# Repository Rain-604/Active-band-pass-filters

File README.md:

# Active Band-Pass Filter Design

## Project Overview
This project showcases a complete hardware design cycle for an Active Band-Pass Filter using the **TL072 Operational Amplifier**. It transition from theoretical calculations to a fully routed PCB layout ready for manufacturing.

## Key Design Features
*   **Active Stage:** Utilizes a TL072 dual op-amp for high input impedance and low noise.
*   **Variable Tuning:** Includes a 10kΩ potentiometer (RV1) for adjustable gain/frequency response tuning.
*   **Signal Integrity:** Optimized 2-layer PCB layout with a dedicated ground plane to minimize noise interference.

## Design Files
### 1. Schematic Design
The schematic features a dual-supply op-amp configuration (powered via the 9V Power block) with a High-Pass stage (C1/R3/R4) and a Low-Pass stage (C2/R5/RV1).

### 2. PCB Layout
The board is designed for manual assembly using through-hole components. 
*   **Trace Width:** Sized for reliable signal delivery and ease of soldering.
*   **Component Placement:** Logically grouped to keep signal paths short.

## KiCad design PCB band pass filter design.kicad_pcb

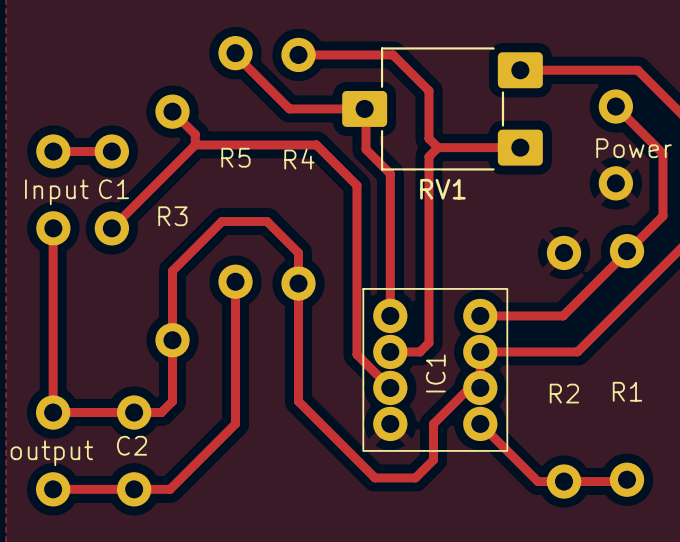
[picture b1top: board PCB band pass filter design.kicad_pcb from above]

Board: 2 copper layers, 12 parts (0 on the bottom side), 9 nets.

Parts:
C1: 470nC; capacitor_hole
C2: 33nC; capacitor_hole
Input: Input; capacitor_hole
Power: Power; capacitor_hole
R1, R2: 1MR; Resistor_hole
R3: 1.6kR; Resistor_hole
R4, R5: 1kR; Resistor_hole
RV1: 10kR; Potentiometer_ACP_CA6-VSMD_Vertical
U1: TL072
output: output; capacitor_hole

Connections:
+9V: Power.2, R1.1, U1.8 (V+)
GND: Power.1, R2.2, U1.4 (V-)
unnamed: C1.2, Input.2
unnamed: C2.2, R5.1, output.2
unnamed: R5.2, RV1.2, U1.1
unnamed: C1.1, R3.1, U1.3 (+)
unnamed: R4.1, RV1.3, U1.2 (-)
unnamed: R1.2, R2.1, U1.5 (+)
unnamed: C2.1, Input.1, R3.2, R4.2, RV1.1, U1.6 (-), U1.7, output.1

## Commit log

2026-05-04 Initialize README with project details
    Added project overview, key design features, and design files for the Active Band-Pass Filter.
